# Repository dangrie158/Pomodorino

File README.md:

# Pomodorino

<br /><span xmlns:dct="http://purl.org/dc/terms/" property="dct:title">USB Power Meter</span> by <a xmlns:cc="http://creativecommons.org/ns#" href="http://www.nupo-artworks.de" property="cc:attributionName" rel="cc:attributionURL">Daniel Grießhaber</a> is licensed under a <a rel="license" href="http://creativecommons.org/licenses/by-sa/4.0/">Creative Commons Attribution-ShareAlike 4.0 International License</a>.<br />Based on a work at <a xmlns:dct="http://purl.org/dc/terms/" href="https://github.com/dangrie158/Pomodorino" rel="dct:source">https://github.com/dangrie158/Pomodorino</a>.

Pomodorino is a small USB device with a full color RGB LED. It main use is to help you to keep track of your time management when using the pomodoro technique, but since it uses an Arduino compatible USB Bootloader you can freely and happily hack the thing to do whatever you want.

## Links

[The Project on Hackaday](https://hackaday.io/project/8196-pomodorino)

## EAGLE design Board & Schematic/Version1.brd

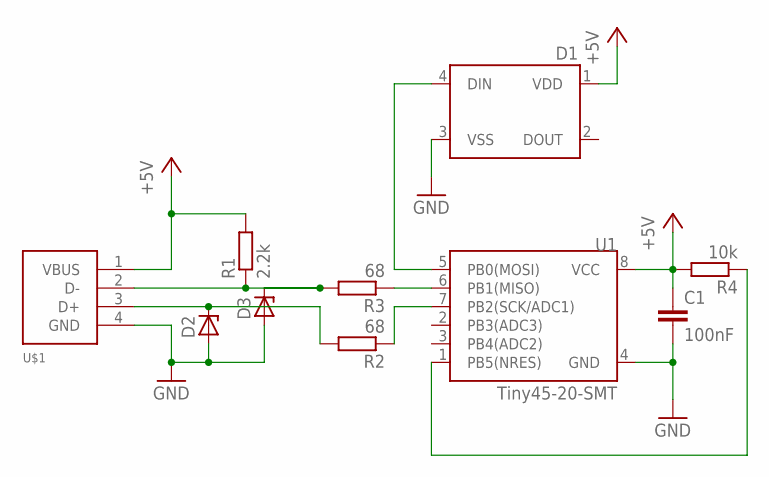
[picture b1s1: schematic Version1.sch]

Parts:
C1: 100nF; C0603
D1: WS2812B
D2, D3: ZENER-DIODESOD80C; SOD80C
R1: 2.2k; R0603
R2, R3: 68; R0603
R4: 10k; R0603
U1: Tiny45-20-SMT; SO08-EIAJ
U$1: USB-CON-4PIN; USB-MALE-A-PCB

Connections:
+5V: C1.1, D1.1 (VDD), R1.2, R4.2, U1.8 (VCC), U$1.1 (VBUS)
GND: C1.2, D1.3 (VSS), D2.A, D3.A, U1.4 (GND), U$1.4 (GND)
unnamed: D3.C, R1.1, R3.2, U$1.2 (D-)
unnamed: D2.C, R2.2, U$1.3 (D+)
unnamed: R3.1, U1.6 (PB1(MISO))
unnamed: R2.1, U1.7 (PB2(SCK/ADC1))
unnamed: R4.1, U1.1 (PB5(NRES))
unnamed: D1.4 (DIN), U1.5 (PB0(MOSI))

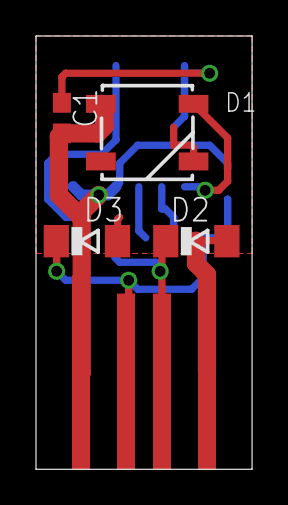
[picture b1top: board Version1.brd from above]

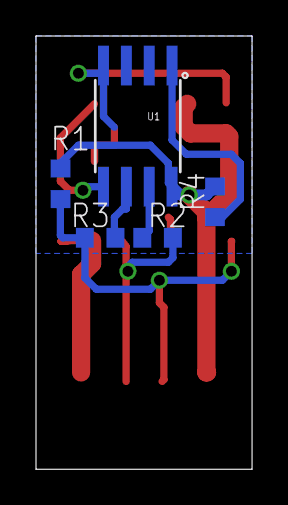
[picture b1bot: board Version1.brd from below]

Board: 2 copper layers, 12.0 x 24.1 mm, 10 parts (5 on the bottom side), 8 nets.

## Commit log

2015-11-07 added Licence information
2015-12-02 fixed zero width polygon
2015-12-02 added Gerbers

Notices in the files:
parts and their libraries:
SparkFun-LED: Licensing: Creative Commons ShareAlike 4.0 International - https://creativecommons.org/licenses/by-sa/4.0
